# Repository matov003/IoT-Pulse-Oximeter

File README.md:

# IoT-Pulse-Oximeter
Design and implementation of an STM32-based IoT reflectance pulse oximeter with custom PCB, Wi-Fi communication and desktop application for SpO₂ and heart rate monitoring. Bachelor's thesis project.

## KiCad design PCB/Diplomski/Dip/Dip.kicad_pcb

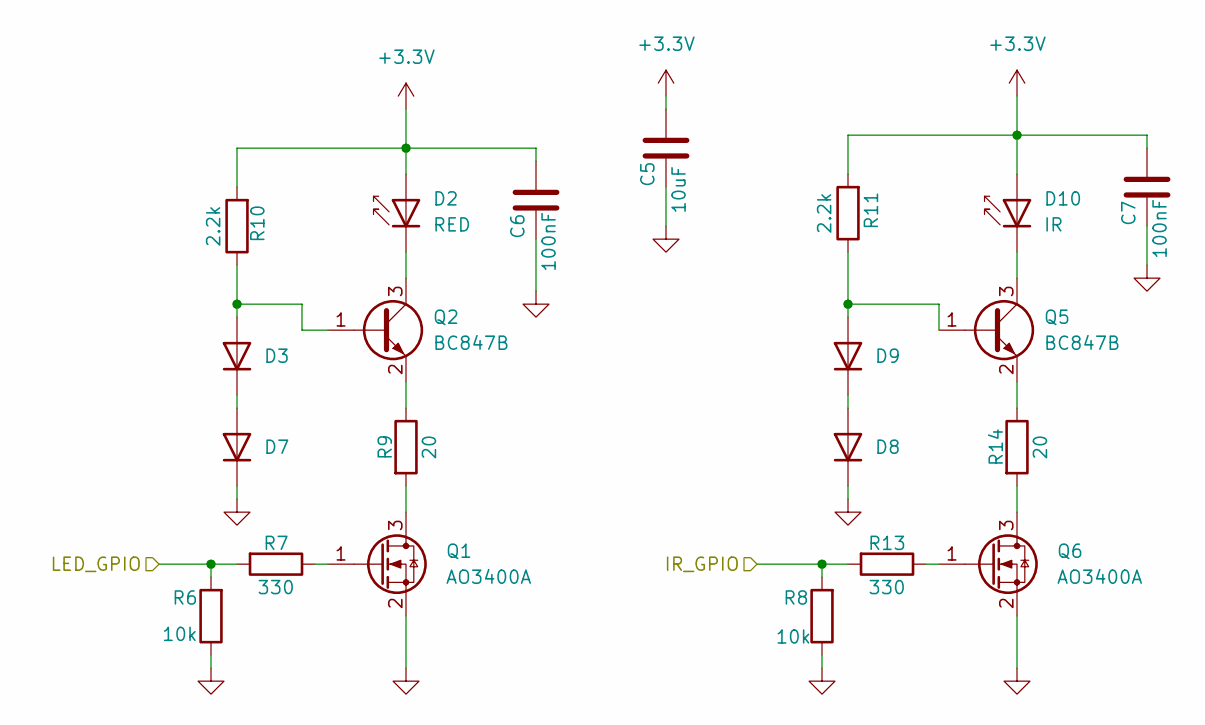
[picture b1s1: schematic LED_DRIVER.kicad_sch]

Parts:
C5: 10uF; C_0805_2012Metric
C6, C7: 100nF; C_0805_2012Metric
D2: RED; LED_D3.0mm_IRBlack
D3, D7, D8, D9: 1N4148WT; D_SOD-523
D10: IR; LED_D3.0mm_IRBlack
Q1, Q6: AO3400A; SOT-23
Q2, Q5: BC847B; SOT-23
R6, R8: 10k; R_0805_2012Metric
R7, R13: 330; R_0805_2012Metric
R9, R14: 20; R_0805_2012Metric
R10, R11: 2.2k; R_0805_2012Metric

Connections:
+3.3V: C5.2, C6.2, C7.2, D2.2 (A), D10.2 (A), R10.2, R11.2; also elsewhere on the board
/LED_DRIVER/IR_GPIO: R8.2, R13.2; also elsewhere on the board
/LED_DRIVER/LED_GPIO: R6.2, R7.2; also elsewhere on the board
GND: C5.1, C6.1, C7.1, D7.1 (K), D8.1 (K), Q1.2 (S), Q6.2 (S), R6.1, R8.1; also elsewhere on the board
unnamed: D2.1 (K), Q2.3 (C)
unnamed: D3.2 (A), Q2.1 (B), R10.1
unnamed: D3.1 (K), D7.2 (A)
unnamed: D8.2 (A), D9.1 (K)
unnamed: D9.2 (A), Q5.1 (B), R11.1
unnamed: D10.1 (K), Q5.3 (C)
unnamed: Q1.3 (D), R9.2
unnamed: Q1.1 (G), R7.1
unnamed: Q2.2 (E), R9.1
unnamed: Q5.2 (E), R14.1
unnamed: Q6.3 (D), R14.2
unnamed: Q6.1 (G), R13.1

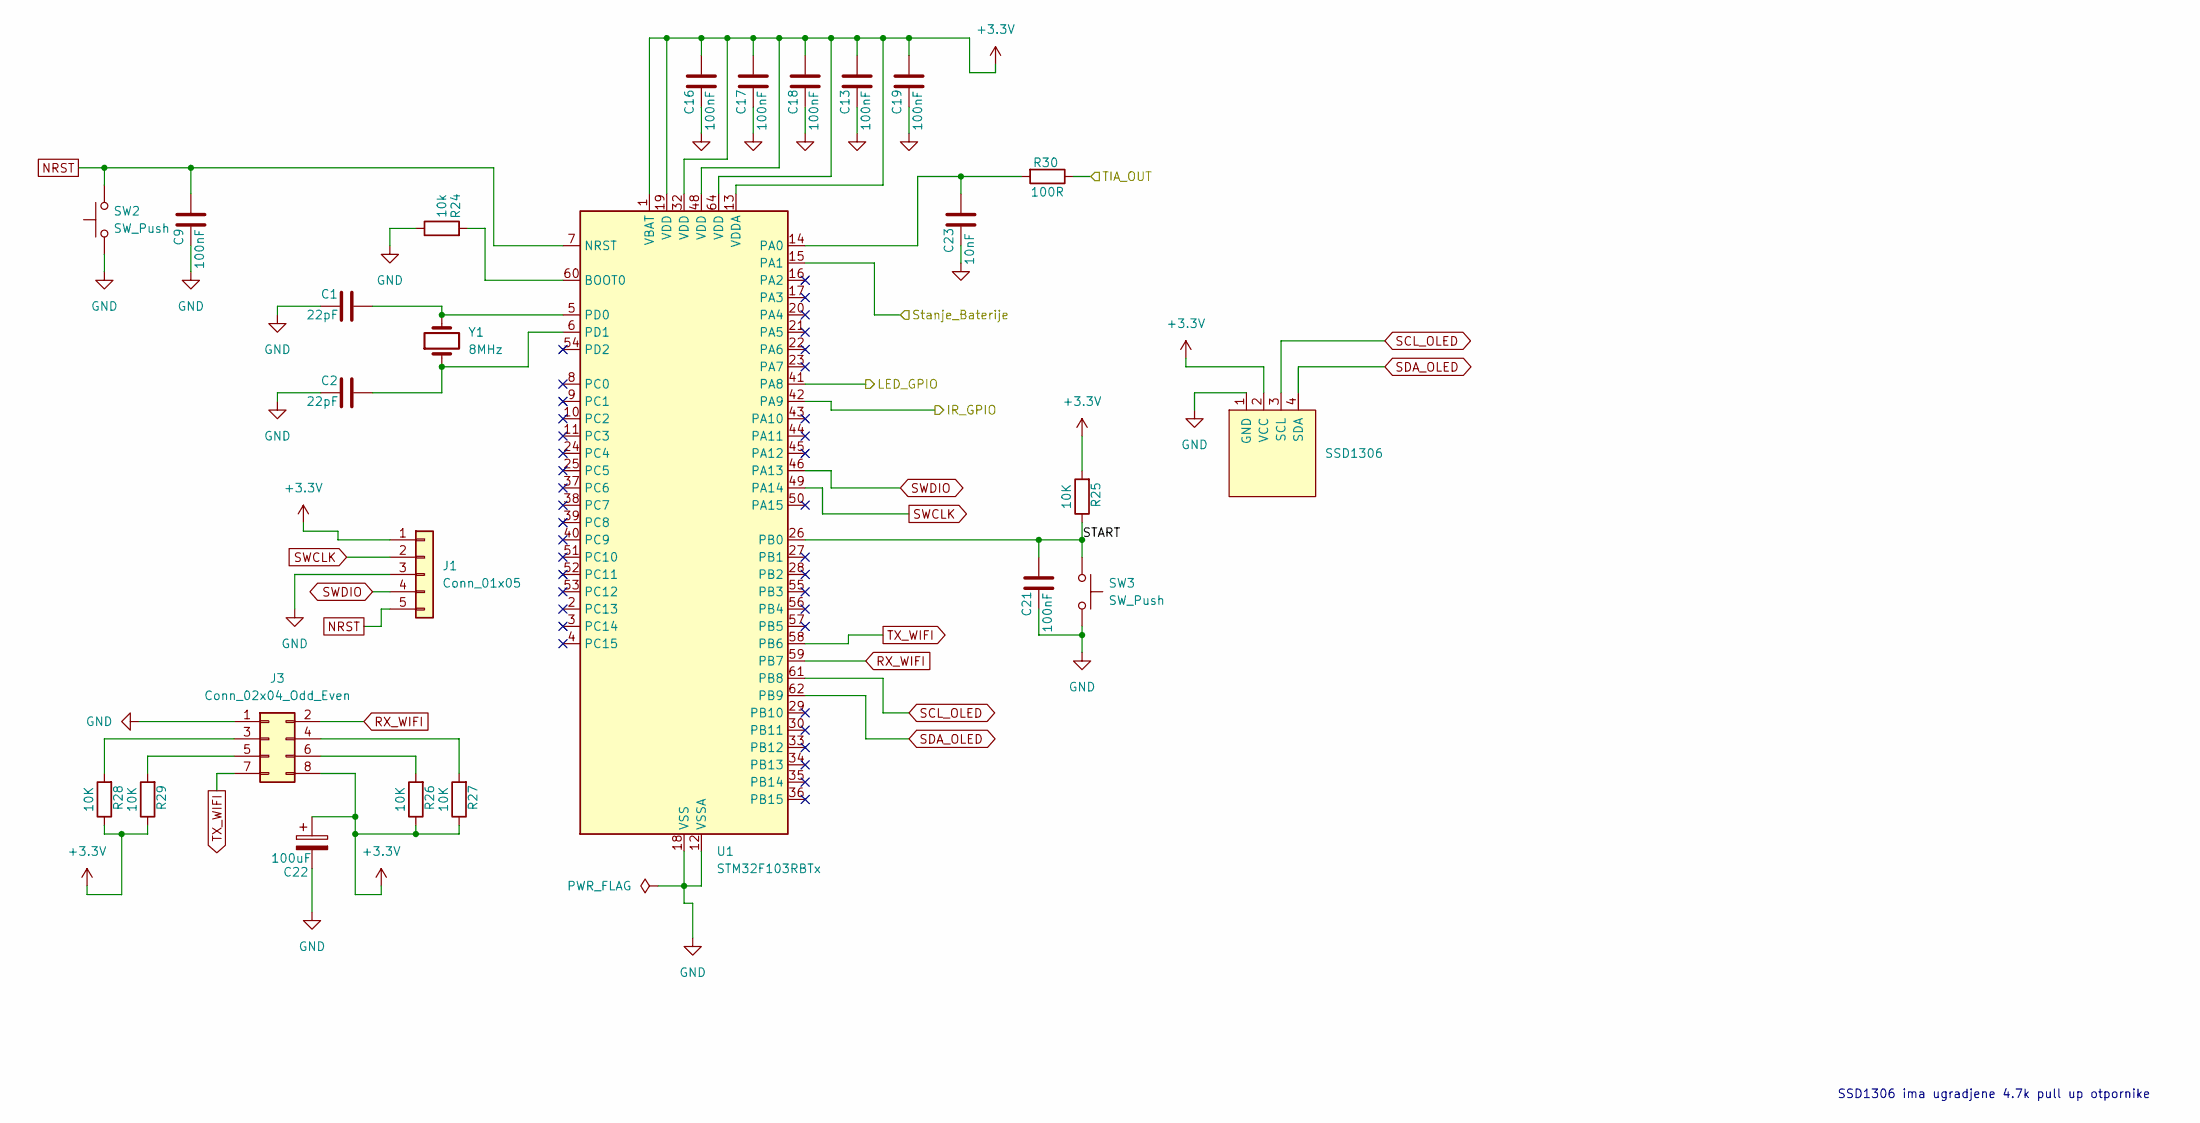
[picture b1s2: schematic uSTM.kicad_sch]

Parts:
Brd1: SSD1306; PinHeader_1x04_P2.54mm_Vertical
C1, C2: 22pF; C_0805_2012Metric
C9, C13, C16, C17, C18, C19, C21: 100nF; C_0805_2012Metric
C22: 100uF; C_1210_3225Metric
C23: 10nF; C_0805_2012Metric
J1: Conn_01x05; PinHeader_1x05_P2.54mm_Vertical
J3: Conn_02x04_Odd_Even; PinSocket_2x04_P2.54mm_Vertical
R24: 10k; R_0805_2012Metric
R25, R26, R27, R28, R29: 10K; R_0805_2012Metric
R30: 100R; R_0805_2012Metric
SW2, SW3: SW_Push; SW_SPST_B3U-1000P
U1: STM32F103RBTx; LQFP-64_10x10mm_P0.5mm
Y1: 8MHz; Crystal_SMD_2012-2Pin_2.0x1.2mm_HandSoldering

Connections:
+3.3V: Brd1.2 (VCC), C13.2, C16.2, C17.2, C18.2, C19.2, C22.1, J1.1, J3.8, R25.2, R26.1, R27.1, R28.1, R29.1, U1.1 (VBAT), U1.13 (VDDA), U1.19 (VDD), U1.32 (VDD), U1.48 (VDD), U1.64 (VDD); also elsewhere on the board
/LED_DRIVER/IR_GPIO: U1.42 (PA9); also elsewhere on the board
/LED_DRIVER/LED_GPIO: U1.41 (PA8); also elsewhere on the board
/Power Supply/Stanje_Baterije: U1.15 (PA1); also elsewhere on the board
/TIA_PF/TIA_OUT: R30.1; also elsewhere on the board
/uSTM/START: C21.2, R25.1, SW3.1, U1.26 (PB0)
GND: Brd1.1 (GND), C1.1, C2.1, C9.1, C13.1, C16.1, C17.1, C18.1, C19.1, C21.1, C22.2, C23.1, J1.3, J3.1, R24.1, SW2.1, SW3.2, U1.12 (VSSA), U1.18 (VSS), U1.31 (VSS), U1.47 (VSS), U1.63 (VSS); also elsewhere on the board
NRST: C9.2, J1.5, SW2.2, U1.7 (NRST)
unnamed: J3.3, R28.2
unnamed: J3.4, R27.2
unnamed: J3.5, R29.2
unnamed: J3.6, R26.2
unnamed: R24.2, U1.60 (BOOT0)
unnamed: C23.2, R30.2, U1.14 (PA0)
unnamed: C1.2, U1.5 (PD0), Y1.2
unnamed: C2.2, U1.6 (PD1), Y1.1
RX_WIFI: J3.2, U1.59 (PB7)
SCL_OLED: Brd1.3 (SCL), U1.61 (PB8)
SDA_OLED: Brd1.4 (SDA), U1.62 (PB9)
SWCLK: J1.2, U1.49 (PA14)
SWDIO: J1.4, U1.46 (PA13)
TX_WIFI: J3.7, U1.58 (PB6)

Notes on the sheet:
SSD1306 ima ugradjene 4.7k pull up otpornike

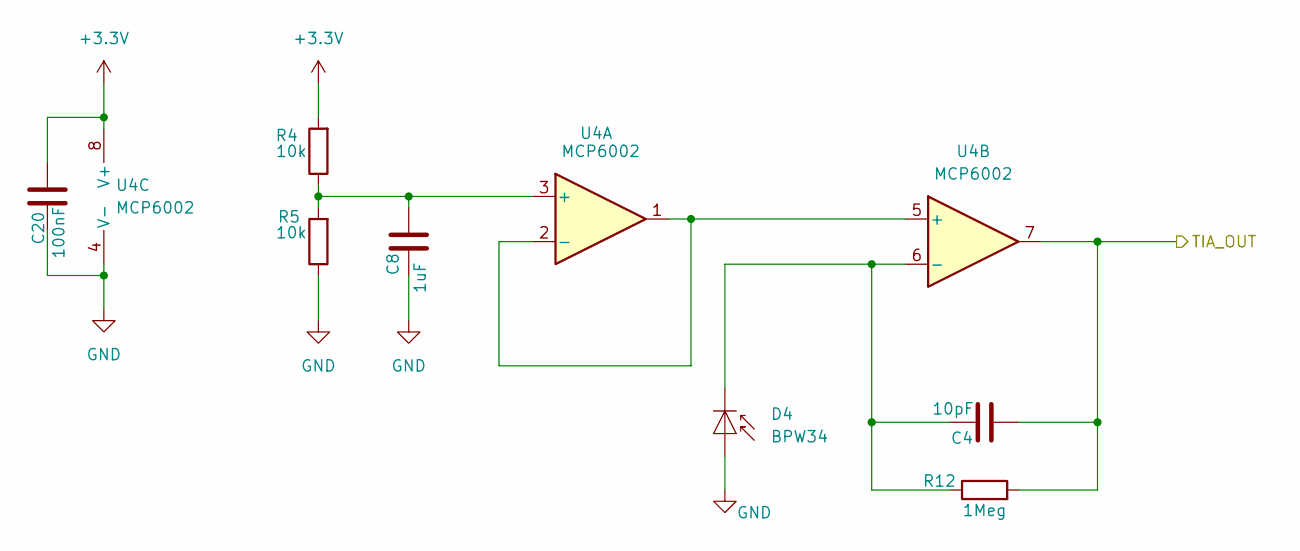
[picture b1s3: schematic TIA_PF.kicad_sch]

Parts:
C4: 10pF; C_0805_2012Metric
C8: 1uF; C_0805_2012Metric
C20: 100nF; C_0805_2012Metric
D4: BPW34; Osram_DIL2_4.3x4.65mm_P5.08mm
R4, R5: 10k; R_0805_2012Metric
R12: 1Meg; R_0805_2012Metric
U4: MCP6002; SOIC-8_3.9x4.9mm_P1.27mm

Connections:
+3.3V: C20.2, R4.2, U4.8 (V+); also elsewhere on the board
/TIA_PF/TIA_OUT: C4.2, R12.2, U4.7; also elsewhere on the board
GND: C8.1, C20.1, D4.2 (A), R5.1, U4.4 (V-); also elsewhere on the board
unnamed: C4.1, D4.1 (K), R12.1, U4.6 (-)
unnamed: C8.2, R4.1, R5.2, U4.3 (+)
unnamed: U4.1, U4.2 (-), U4.5 (+)

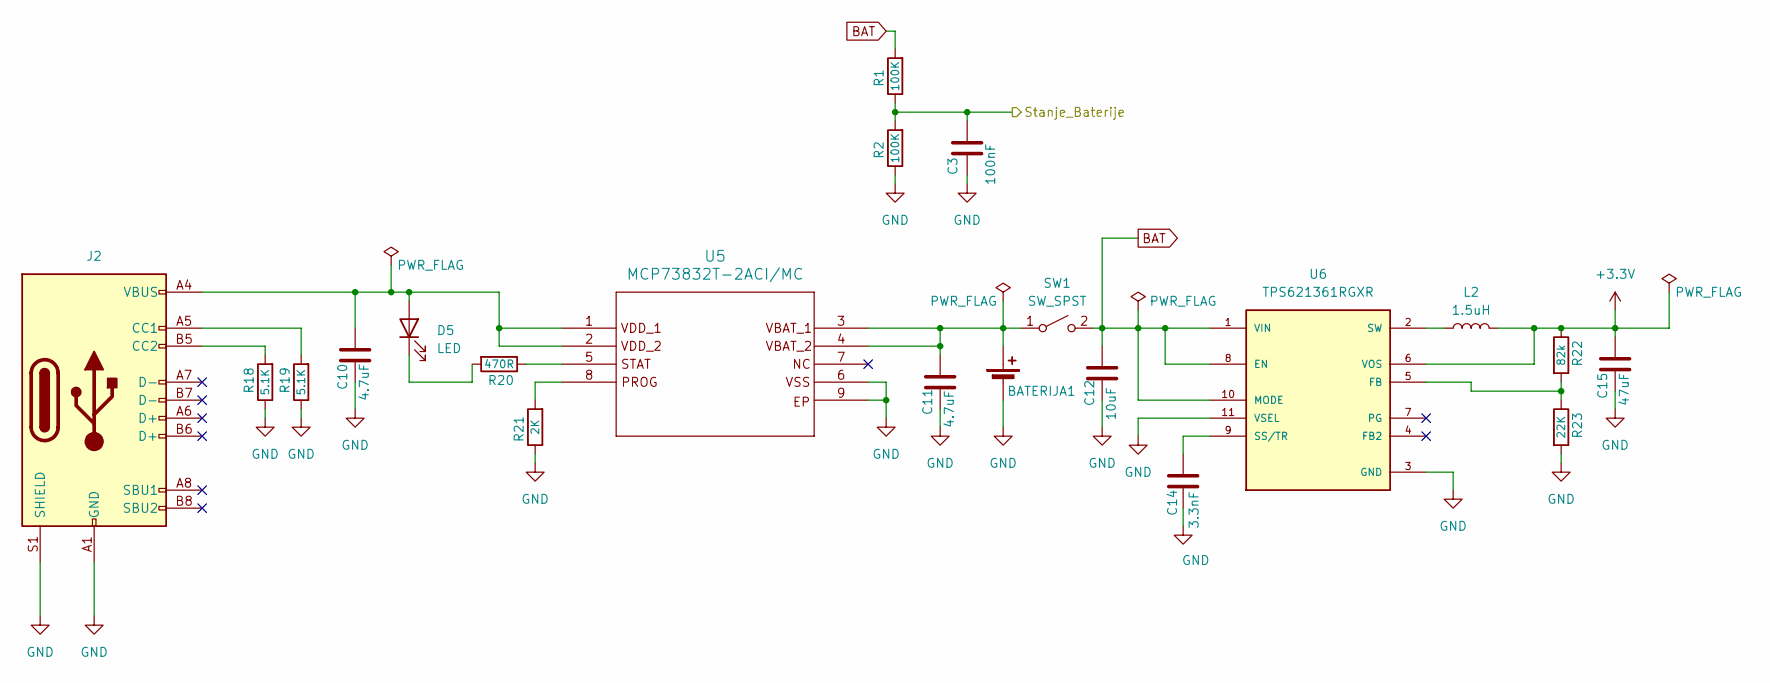
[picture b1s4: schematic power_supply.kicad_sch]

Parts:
BATERIJA1: Battery_Cell; JST_SH_SM02B-SRSS-TB_1x02-1MP_P1.00mm_Horizontal
C3: 100nF; C_0805_2012Metric
C10, C11: 4.7uF; C_0805_2012Metric
C12: 10uF; C_0805_2012Metric
C14: 3.3nF; C_0805_2012Metric
C15: 47uF; C_1210_3225Metric
D5: LED; LED_0805_2012Metric
J2: USB_C_Receptacle_USB2.0_16P; USB_C_Receptacle_GCT_USB4085
L2: 1.5uH; L_1210_3225Metric
R1, R2: 100K; R_0805_2012Metric
R18, R19: 5.1K; R_0805_2012Metric
R20: 470R; R_0805_2012Metric
R21: 2K; R_0805_2012Metric
R22: 82k; R_0805_2012Metric
R23: 22K; R_0805_2012Metric
SW1: SW_SPST; PinHeader_1x02_P2.54mm_Vertical
U5: MCP73832T-2ACI/MC; DFN-8-1EP_3x2mm_P0.5mm_EP1.75x1.45mm
U6: TPS621361RGXR; VREG_TPS621361RGXR; PARTREV March 2017

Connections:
+3.3V: C15.2, L2.2, R22.1, U6.6 (VOS); also elsewhere on the board
/Power Supply/Stanje_Baterije: C3.2, R1.1, R2.2; also elsewhere on the board
BAT: C12.2, R1.2, SW1.2 (B), U6.1 (VIN), U6.8 (EN), U6.10 (MODE)
GND: BATERIJA1.2 (-), C3.1, C10.1, C11.1, C12.1, C14.1, C15.1, J2.A1 (GND), J2.A12 (GND), J2.B1 (GND), J2.B12 (GND), J2.S1 (SHIELD), R2.1, R18.1, R19.1, R21.1, R23.2, U5.6, U5.9, U6.3 (GND), U6.11 (VSEL); also elsewhere on the board
unnamed: BATERIJA1.1 (+), C11.2, SW1.1 (A), U5.3, U5.4
unnamed: C10.2, D5.2 (A), J2.A4 (VBUS), J2.A9 (VBUS), J2.B4 (VBUS), J2.B9 (VBUS), U5.1, U5.2
unnamed: D5.1 (K), R20.2
unnamed: J2.A5 (CC1), R19.2
unnamed: J2.B5 (CC2), R18.2
unnamed: R20.1, U5.5
unnamed: R21.2, U5.8
unnamed: R22.2, R23.1, U6.5 (FB)
unnamed: C14.2, U6.9 (SS/TR)
unnamed: L2.1, U6.2 (SW)

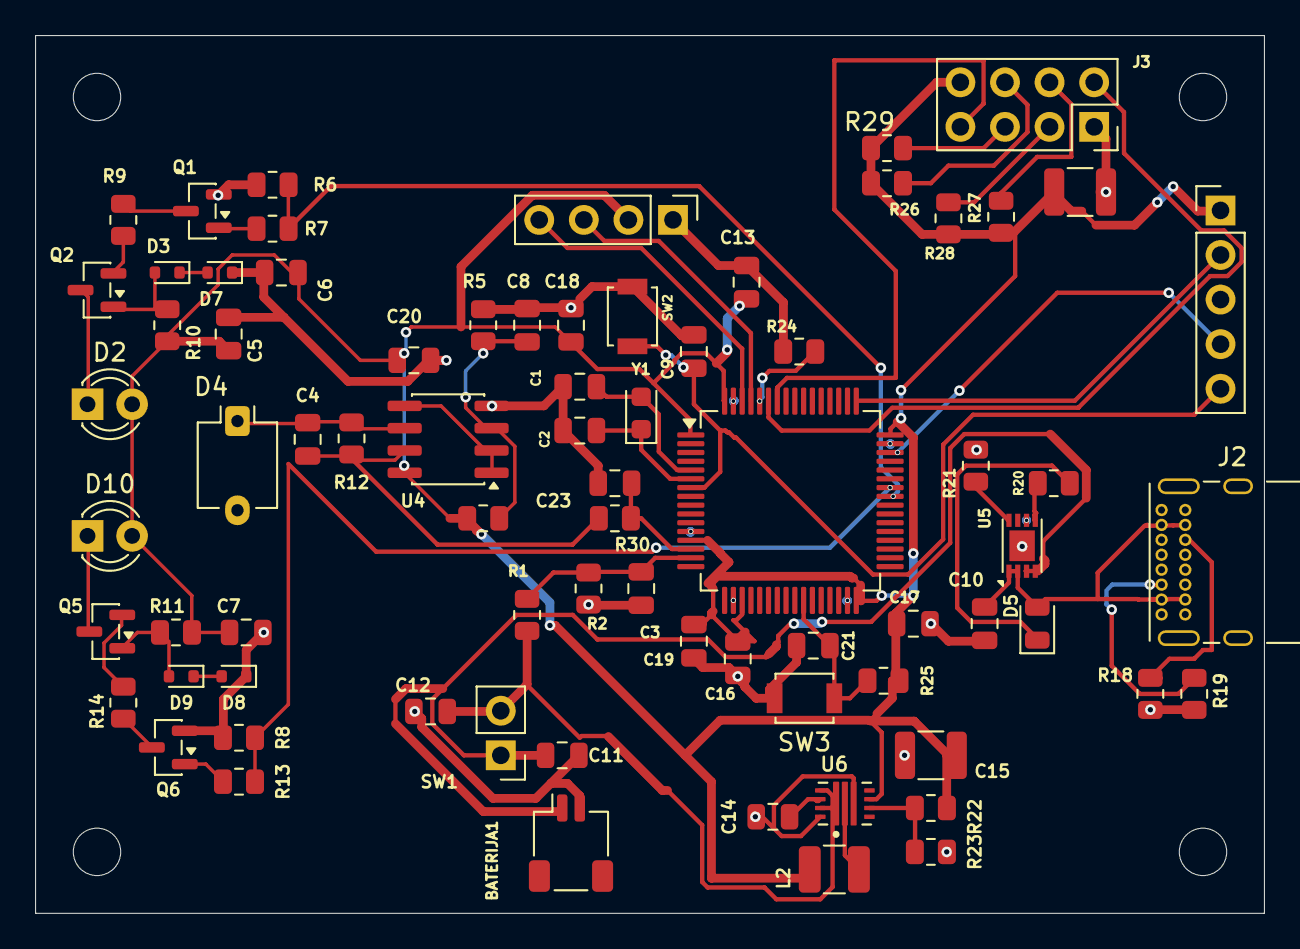
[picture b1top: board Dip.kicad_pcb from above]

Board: 2 copper layers, 70.0 x 50.0 mm, 75 parts (0 on the bottom side), 48 nets.

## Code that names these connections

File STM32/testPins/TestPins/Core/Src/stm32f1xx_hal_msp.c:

/* USER CODE BEGIN Header */
/**
  ******************************************************************************
  * @file         stm32f1xx_hal_msp.c
  * @brief        This file provides code for the MSP Initialization
  *               and de-Initialization codes.
  ******************************************************************************
  * @attention
  *
  * Copyright (c) 2026 STMicroelectronics.
  * All rights reserved.
  *
  * This software is licensed under terms that can be found in the LICENSE file
  * in the root directory of this software component.
  * If no LICENSE file comes with this software, it is provided AS-IS.
  *
  ******************************************************************************
  */
/* USER CODE END Header */
/* Includes ------------------------------------------------------------------*/
#include "main.h"
/* USER CODE BEGIN Includes */

/* USER CODE END Includes */

/* Private typedef -----------------------------------------------------------*/
/* USER CODE BEGIN TD */

/* USER CODE END TD */

/* Private define ------------------------------------------------------------*/
/* USER CODE BEGIN Define */

/* USER CODE END Define */

/* Private macro -------------------------------------------------------------*/
/* USER CODE BEGIN Macro */

/* USER CODE END Macro */

/* Private variables ---------------------------------------------------------*/
/* USER CODE BEGIN PV */

/* USER CODE END PV */

/* Private function prototypes -----------------------------------------------*/
/* USER CODE BEGIN PFP */

/* USER CODE END PFP */

/* External functions --------------------------------------------------------*/
/* USER CODE BEGIN ExternalFunctions */

/* USER CODE END ExternalFunctions */

/* USER CODE BEGIN 0 */

/* USER CODE END 0 */

void HAL_TIM_MspPostInit(TIM_HandleTypeDef *htim);
                    /**
  * Initializes the Global MSP.
  */
void HAL_MspInit(void)
{

  /* USER CODE BEGIN MspInit 0 */

  /* USER CODE END MspInit 0 */

  __HAL_RCC_AFIO_CLK_ENABLE();
  __HAL_RCC_PWR_CLK_ENABLE();

  /* System interrupt init*/

  /** DISABLE: JTAG-DP Disabled and SW-DP Disabled
  */
  __HAL_AFIO_REMAP_SWJ_DISABLE();

  /* USER CODE BEGIN MspInit 1 */

  /* USER CODE END MspInit 1 */
}

/**
  * @brief ADC MSP Initialization
  * This function configures the hardware resources used in this example
  * @param hadc: ADC handle pointer
  * @retval None
  */
void HAL_ADC_MspInit(ADC_HandleTypeDef* hadc)
{
  GPIO_InitTypeDef GPIO_InitStruct = {0};
  if(hadc->Instance==ADC1)
  {
    /* USER CODE BEGIN ADC1_MspInit 0 */

    /* USER CODE END ADC1_MspInit 0 */
    /* Peripheral clock enable */
    __HAL_RCC_ADC1_CLK_ENABLE();

    __HAL_RCC_GPIOA_CLK_ENABLE();
    /**ADC1 GPIO Configuration
    PA0-WKUP     ------> ADC1_IN0
    */
    GPIO_InitStruct.Pin = GPIO_PIN_0;
    GPIO_InitStruct.Mode = GPIO_MODE_ANALOG;
    HAL_GPIO_Init(GPIOA, &GPIO_InitStruct);

    /* USER CODE BEGIN ADC1_MspInit 1 */

    /* USER CODE END ADC1_MspInit 1 */

  }

}

/**
  * @brief ADC MSP De-Initialization
  * This function freeze the hardware resources used in this example
  * @param hadc: ADC handle pointer
  * @retval None
  */
void HAL_ADC_MspDeInit(ADC_HandleTypeDef* hadc)
{
  if(hadc->Instance==ADC1)
  {
    /* USER CODE BEGIN ADC1_MspDeInit 0 */

    /* USER CODE END ADC1_MspDeInit 0 */
    /* Peripheral clock disable */
    __HAL_RCC_ADC1_CLK_DISABLE();

    /**ADC1 GPIO Configuration
    PA0-WKUP     ------> ADC1_IN0
    */
    HAL_GPIO_DeInit(GPIOA, GPIO_PIN_0);

    /* USER CODE BEGIN ADC1_MspDeInit 1 */

    /* USER CODE END ADC1_MspDeInit 1 */
  }

}

/**
  * @brief I2C MSP Initialization
  * This function configures the hardware resources used in this example
  * @param hi2c: I2C handle pointer
  * @retval None
  */
void HAL_I2C_MspInit(I2C_HandleTypeDef* hi2c)
{
  GPIO_InitTypeDef GPIO_InitStruct = {0};
  if(hi2c->Instance==I2C2)
  {
    /* USER CODE BEGIN I2C2_MspInit 0 */

    /* USER CODE END I2C2_MspInit 0 */

    __HAL_RCC_GPIOB_CLK_ENABLE();
    /**I2C2 GPIO Configuration
    PB10     ------> I2C2_SCL
    PB11     ------> I2C2_SDA
    */
    GPIO_InitStruct.Pin = GPIO_PIN_10|GPIO_PIN_11;
    GPIO_InitStruct.Mode = GPIO_MODE_AF_OD;
    GPIO_InitStruct.Speed = GPIO_SPEED_FREQ_HIGH;
    HAL_GPIO_Init(GPIOB, &GPIO_InitStruct);

    /* Peripheral clock enable */
    __HAL_RCC_I2C2_CLK_ENABLE();
    /* USER CODE BEGIN I2C2_MspInit 1 */

    /* USER CODE END I2C2_MspInit 1 */

  }

}

/**
  * @brief I2C MSP De-Initialization
  * This function freeze the hardware resources used in this example
  * @param hi2c: I2C handle pointer
  * @retval None
  */
void HAL_I2C_MspDeInit(I2C_HandleTypeDef* hi2c)
{
  if(hi2c->Instance==I2C2)
  {
    /* USER CODE BEGIN I2C2_MspDeInit 0 */

    /* USER CODE END I2C2_MspDeInit 0 */
    /* Peripheral clock disable */
    __HAL_RCC_I2C2_CLK_DISABLE();

    /**I2C2 GPIO Configuration
    PB10     ------> I2C2_SCL
    PB11     ------> I2C2_SDA
    */
    HAL_GPIO_DeInit(GPIOB, GPIO_PIN_10);

    HAL_GPIO_DeInit(GPIOB, GPIO_PIN_11);

    /* USER CODE BEGIN I2C2_MspDeInit 1 */

    /* USER CODE END I2C2_MspDeInit 1 */
  }

}

/**
  * @brief TIM_Base MSP Initialization
  * This function configures the hardware resources used in this example
  * @param htim_base: TIM_Base handle pointer
  * @retval None
  */
void HAL_TIM_Base_MspInit(TIM_HandleTypeDef* htim_base)
{
  if(htim_base->Instance==TIM1)
  {
    /* USER CODE BEGIN TIM1_MspInit 0 */

    /* USER CODE END TIM1_MspInit 0 */
    /* Peripheral clock enable */
    __HAL_RCC_TIM1_CLK_ENABLE();
    /* USER CODE BEGIN TIM1_MspInit 1 */

    /* USER CODE END TIM1_MspInit 1 */

  }

}

void HAL_TIM_MspPostInit(TIM_HandleTypeDef* htim)
{
  GPIO_InitTypeDef GPIO_InitStruct = {0};
  if(htim->Instance==TIM1)
  {
    /* USER CODE BEGIN TIM1_MspPostInit 0 */

    /* USER CODE END TIM1_MspPostInit 0 */

    __HAL_RCC_GPIOA_CLK_ENABLE();
    /**TIM1 GPIO Configuration
    PA8     ------> TIM1_CH1
    PA9     ------> TIM1_CH2
    */
    GPIO_InitStruct.Pin = GPIO_PIN_8|GPIO_PIN_9;
    GPIO_InitStruct.Mode = GPIO_MODE_AF_PP;
    GPIO_InitStruct.Speed = GPIO_SPEED_FREQ_LOW;
    HAL_GPIO_Init(GPIOA, &GPIO_InitStruct);

    /* USER CODE BEGIN TIM1_MspPostInit 1 */

    /* USER CODE END TIM1_MspPostInit 1 */
  }

}
/**
  * @brief TIM_Base MSP De-Initialization
  * This function freeze the hardware resources used in this example
  * @param htim_base: TIM_Base handle pointer
  * @retval None
  */
void HAL_TIM_Base_MspDeInit(TIM_HandleTypeDef* htim_base)
{
  if(htim_base->Instance==TIM1)
  {
    /* USER CODE BEGIN TIM1_MspDeInit 0 */

    /* USER CODE END TIM1_MspDeInit 0 */
    /* Peripheral clock disable */
    __HAL_RCC_TIM1_CLK_DISABLE();
    /* USER CODE BEGIN TIM1_MspDeInit 1 */

    /* USER CODE END TIM1_MspDeInit 1 */
  }

}

/**
  * @brief UART MSP Initialization
  * This function configures the hardware resources used in this example
  * @param huart: UART handle pointer
  * @retval None
  */
void HAL_UART_MspInit(UART_HandleTypeDef* huart)
{
  GPIO_InitTypeDef GPIO_InitStruct = {0};
  if(huart->Instance==USART1)
  {
    /* USER CODE BEGIN USART1_MspInit 0 */

    /* USER CODE END USART1_MspInit 0 */
    /* Peripheral clock enable */
    __HAL_RCC_USART1_CLK_ENABLE();

    __HAL_RCC_GPIOB_CLK_ENABLE();
    /**USART1 GPIO Configuration
    PB6     ------> USART1_TX
    PB7     ------> USART1_RX
    */
    GPIO_InitStruct.Pin = GPIO_PIN_6;
    GPIO_InitStruct.Mode = GPIO_MODE_AF_PP;
    GPIO_InitStruct.Speed = GPIO_SPEED_FREQ_HIGH;
    HAL_GPIO_Init(GPIOB, &GPIO_InitStruct);

    GPIO_InitStruct.Pin = GPIO_PIN_7;
    GPIO_InitStruct.Mode = GPIO_MODE_INPUT;
    GPIO_InitStruct.Pull = GPIO_NOPULL;
    HAL_GPIO_Init(GPIOB, &GPIO_InitStruct);

    __HAL_AFIO_REMAP_USART1_ENABLE();

    /* USART1 interrupt Init */
    HAL_NVIC_SetPriority(USART1_IRQn, 0, 0);
    HAL_NVIC_EnableIRQ(USART1_IRQn);
    /* USER CODE BEGIN USART1_MspInit 1 */

    /* USER CODE END USART1_MspInit 1 */

  }

}

/**
  * @brief UART MSP De-Initialization
  * This function freeze the hardware resources used in this example
  * @param huart: UART handle pointer
  * @retval None
  */
void HAL_UART_MspDeInit(UART_HandleTypeDef* huart)
{
  if(huart->Instance==USART1)
  {
    /* USER CODE BEGIN USART1_MspDeInit 0 */

    /* USER CODE END USART1_MspDeInit 0 */
    /* Peripheral clock disable */
    __HAL_RCC_USART1_CLK_DISABLE();

    /**USART1 GPIO Configuration
    PB6     ------> USART1_TX
    PB7     ------> USART1_RX
    */
    HAL_GPIO_DeInit(GPIOB, GPIO_PIN_6|GPIO_PIN_7);

    /* USART1 interrupt DeInit */
    HAL_NVIC_DisableIRQ(USART1_IRQn);
    /* USER CODE BEGIN USART1_MspDeInit 1 */

    /* USER CODE END USART1_MspDeInit 1 */
  }

}

/* USER CODE BEGIN 1 */

/* USER CODE END 1 */
